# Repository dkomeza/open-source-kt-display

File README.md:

[![Contributors][contributors-shield]][contributors-url]
[![Forks][forks-shield]][forks-url]
[![Issues][issues-shield]][issues-url]
[![MIT License][license-shield]][license-url]

# Open-Source KT Display
Open source display firmware for E-Bike KT controllers. Made for Arduino with compatible SPI Display. 

**NOTE**: _This repository is no longer supported or updated by @dkomeza. It has been moved to [oskd](https://github.com/dkomeza/oskd) where it will be maintained from now on (21.01.2024). If you wish to continue to develop this code yourself, I recommend you fork it._</code>

<br>

## TL;DR
This is an open source display created for KT controllers. It uses ESP32 and a compatible SPI display. It is a work in progress and is not yet ready for production.

<br>

## Table of contents

- [Open-Source KT Display](#open-source-kt-display)
  - [TL;DR](#tldr)
  - [Table of contents](#table-of-contents)
  - [About the project](#about-the-project)
    - [Features](#features)
    - [Future of the project](#future-of-the-project)

<br><br>

## About the project

This project started as a way to use a torque sensor with the KT controllers. Later I decided to create a full featured display for the KT controllers. The goal is to create a display that is open source and can be used with any KT controller. It will also have a torque sensor input and a legal speed and power limiter. It is still a work in progress and is not yet ready for production. For more information about the project, please visit the [wiki](https://github.com/dkomeza/open-source-kt-display/wiki).

<br>

### Features
 - Open source
 - Cheap to build yourself
 - Has a torque sensor input
 - Has a legal speed and power limiter
<br>

### Future of the project

As for now, the project is still in development. I am working on the firmware and the hardware. The firmware is finally usable but still not final and the hardware is not yet ready for production. On the software side I am currently working on the settings menu and bug fixes, and on the hardware I am working on the PCB design and the case design. I will release the firmware and the hardware design files when they are ready. I will also release a tutorial on how to build the display yourself.

<!-- MARKDOWN LINKS & IMAGES -->
<!-- https://www.markdownguide.org/basic-syntax/#reference-style-links -->
[contributors-shield]: https://img.shields.io/github/contributors/dkomeza/open-source-kt-display.svg?style=for-the-badge
[contributors-url]: https://github.com/dkomeza/open-source-kt-display/graphs/contributors
[forks-shield]: https://img.shields.io/github/forks/dkomeza/open-source-kt-display.svg?style=for-the-badge
[forks-url]: https://github.com/dkomeza/open-source-kt-display/network/members
[stars-shield]: https://img.shields.io/github/stars/dkomeza/open-source-kt-display.svg?style=for-the-badge
[stars-url]: https://github.com/dkomeza/open-source-kt-display/stargazers
[issues-shield]: https://img.shields.io/github/issues/dkomeza/open-source-kt-display.svg?style=for-the-badge
[issues-url]: https://github.com/dkomeza/open-source-kt-display/issues
[license-shield]: https://img.shields.io/github/license/dkomeza/open-source-kt-display.svg?style=for-the-badge
[license-url]: https://github.com/dkomeza/open-source-kt-display/blob/master/LICENSE.txt

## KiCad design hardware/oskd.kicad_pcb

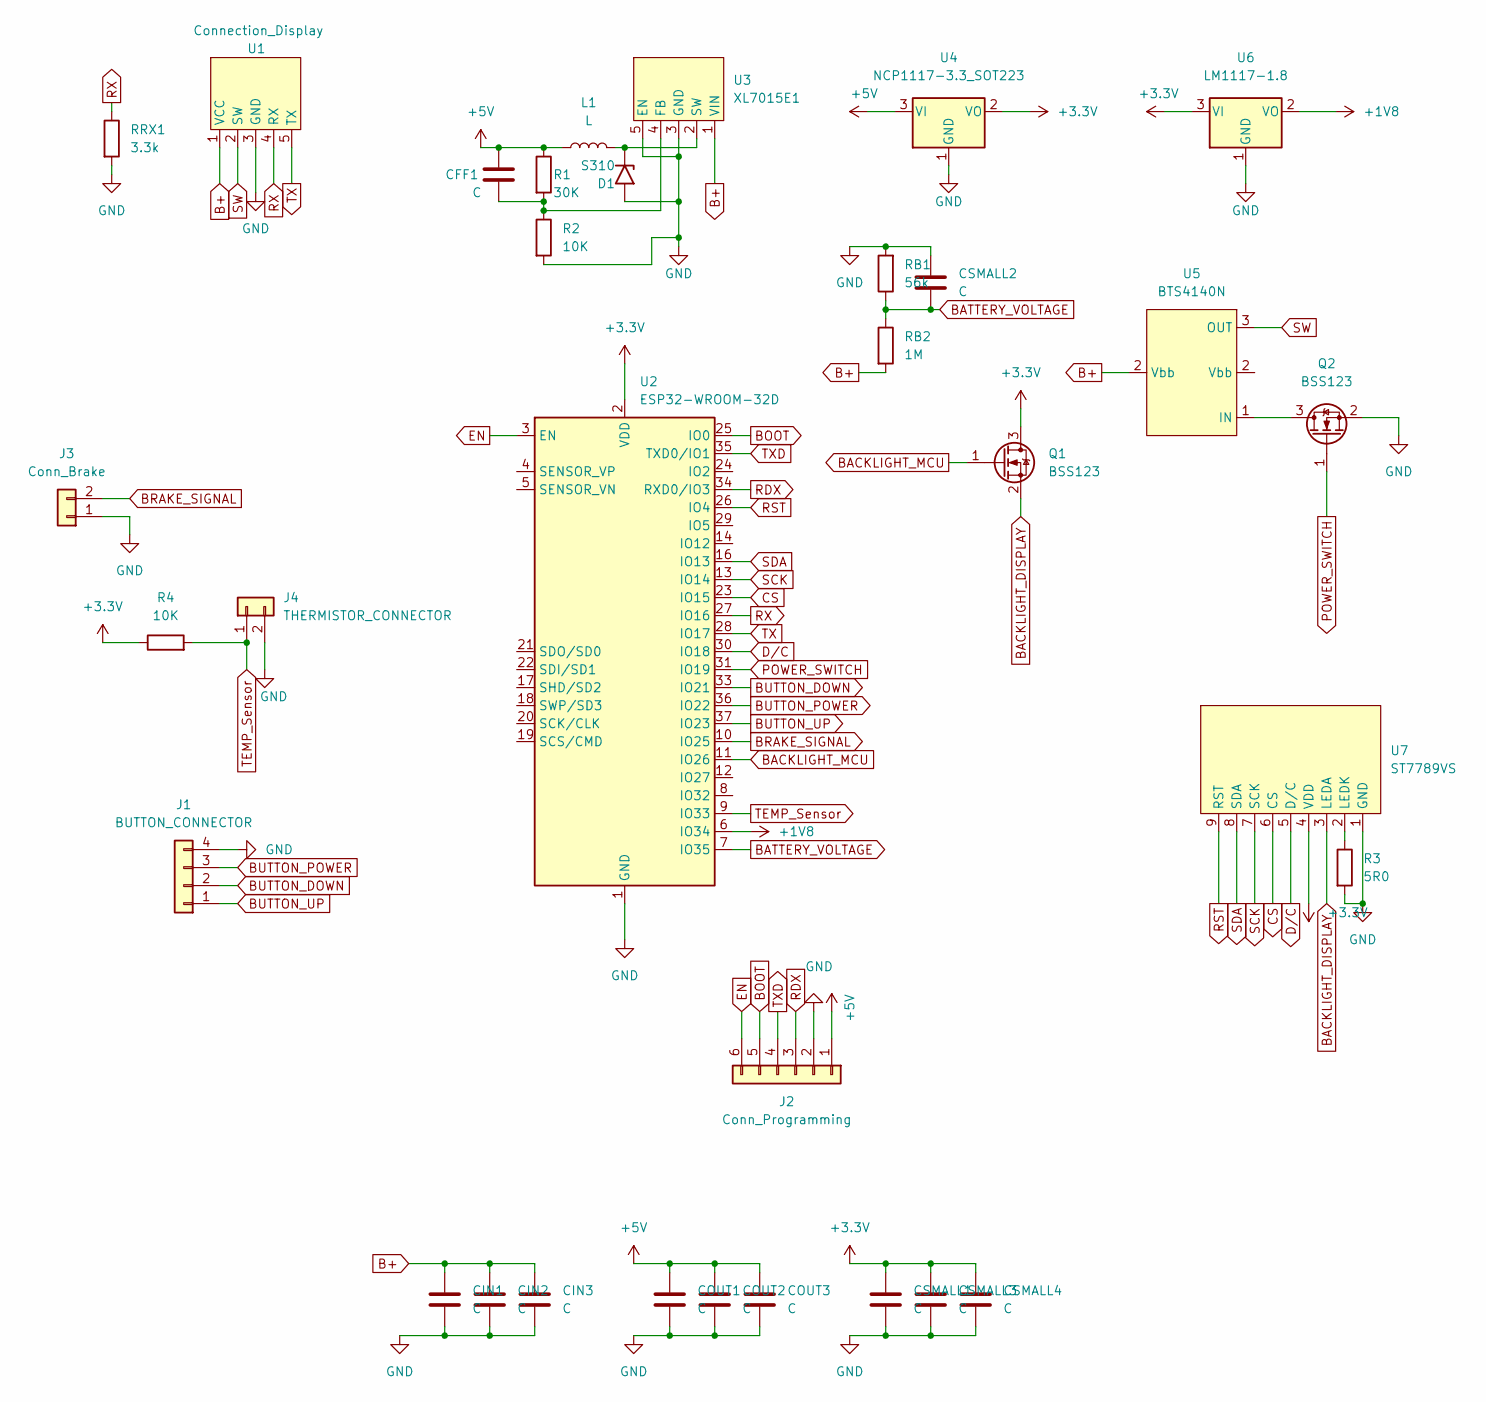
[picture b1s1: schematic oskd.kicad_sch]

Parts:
CFF1: C; C_1206_3216Metric_Pad1.33x1.80mm_HandSolder
CIN1, CIN2, CIN3: C; C_1210_3225Metric_Pad1.33x2.70mm_HandSolder
COUT1, COUT2, COUT3: C; C_1210_3225Metric_Pad1.33x2.70mm_HandSolder
CSMALL1, CSMALL2, CSMALL3, CSMALL4: C; C_1206_3216Metric
D1: S310; S2M
J1: BUTTON_CONNECTOR; SolderWire-1x4-buttons
J2: Conn_Programming; PinHeader_1x06_P2.54mm_Horizontal
J3: Conn_Brake; SolderWire-0.25sqmm_1x02_P4.5mm_D0.65mm_OD2mm
J4: THERMISTOR_CONNECTOR; SolderWire-0.25sqmm_1x02_P4.2mm_D0.65mm_OD1.7mm
L1: L; L_7.3x7.3_H3.5
Q1, Q2: BSS123; SOT-23
R1: 30K; R_1206_3216Metric_Pad1.30x1.75mm_HandSolder
R2, R4: 10K; R_1206_3216Metric_Pad1.30x1.75mm_HandSolder
R3: 5R0; R_1206_3216Metric_Pad1.30x1.75mm_HandSolder
RB1: 56k; R_1206_3216Metric_Pad1.30x1.75mm_HandSolder
RB2: 1M; R_1206_3216Metric_Pad1.30x1.75mm_HandSolder
RRX1: 3.3k; R_1206_3216Metric_Pad1.30x1.75mm_HandSolder
U1: Connection_Display; SolderWire-1x5-display
U2: ESP32-WROOM-32D; ESP32-WROOM-32
U3: XL7015E1; TO-252-5_TabPin3
U4: NCP1117-3.3_SOT223; SOT-223-3_TabPin2
U5: BTS4140N; SOT-223-3_TabPin2
U6: LM1117-1.8; SOT-223-3_TabPin2
U7: ST7789VS; ST7789V2

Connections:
+1V8: U2.6 (IO34), U6.2 (VO)
+3.3V: CSMALL1.1, CSMALL3.1, CSMALL4.1, Q1.3 (D), R4.1, U2.2 (VDD), U4.2 (VO), U6.3 (VI), U7.4 (VDD)
+5V: CFF1.2, COUT1.1, COUT2.1, COUT3.1, J2.1, L1.1, R1.1, U4.3 (VI)
B+: CIN1.1, CIN2.1, CIN3.1, RB2.2, U1.1 (VCC), U3.1 (VIN), U5.2 (Vbb)
BACKLIGHT_DISPLAY: Q1.2 (S), U7.3 (LEDA)
BACKLIGHT_MCU: Q1.1 (G), U2.11 (IO26)
BATTERY_VOLTAGE: CSMALL2.2, RB1.1, RB2.1, U2.7 (IO35)
BOOT: J2.5, U2.25 (IO0)
BRAKE_SIGNAL: J3.2, U2.10 (IO25)
BUTTON_DOWN: J1.2, U2.33 (IO21)
BUTTON_POWER: J1.3, U2.36 (IO22)
BUTTON_UP: J1.1, U2.37 (IO23)
CS: U2.23 (IO15), U7.6 (CS)
D/C: U2.30 (IO18), U7.5 (D/C)
EN: J2.6, U2.3 (EN)
GND: CIN1.2, CIN2.2, CIN3.2, COUT1.2, COUT2.2, COUT3.2, CSMALL1.2, CSMALL2.1, CSMALL3.2, CSMALL4.2, D1.2 (A2), J1.4, J2.2, J3.1, J4.2, Q2.2 (S), R2.2, R3.2, RB1.2, RRX1.2, U1.3 (GND), U2.1 (GND), U2.15 (GND), U2.38 (GND), U2.39 (GND), U3.3 (GND), U3.5 (EN), U4.1 (GND), U6.1 (GND), U7.1 (GND)
unnamed: CFF1.1, R1.2, R2.1, U3.4 (FB)
unnamed: D1.1 (A1), L1.2, U3.2 (SW)
unnamed: Q2.3 (D), U5.1 (IN)
unnamed: R3.1, U7.2 (LEDK)
POWER_SWITCH: Q2.1 (G), U2.31 (IO19)
RDX: J2.3, U2.34 (RXD0/IO3)
RST: U2.26 (IO4), U7.9 (RST)
RX: RRX1.1, U1.4 (RX), U2.27 (IO16)
SCK: U2.13 (IO14), U7.7 (SCK)
SDA: U2.16 (IO13), U7.8 (SDA)
SW: U1.2 (SW), U5.3 (OUT)
TEMP_Sensor: J4.1, R4.2, U2.9 (IO33)
TX: U1.5 (TX), U2.28 (IO17)
TXD: J2.4, U2.35 (TXD0/IO1)

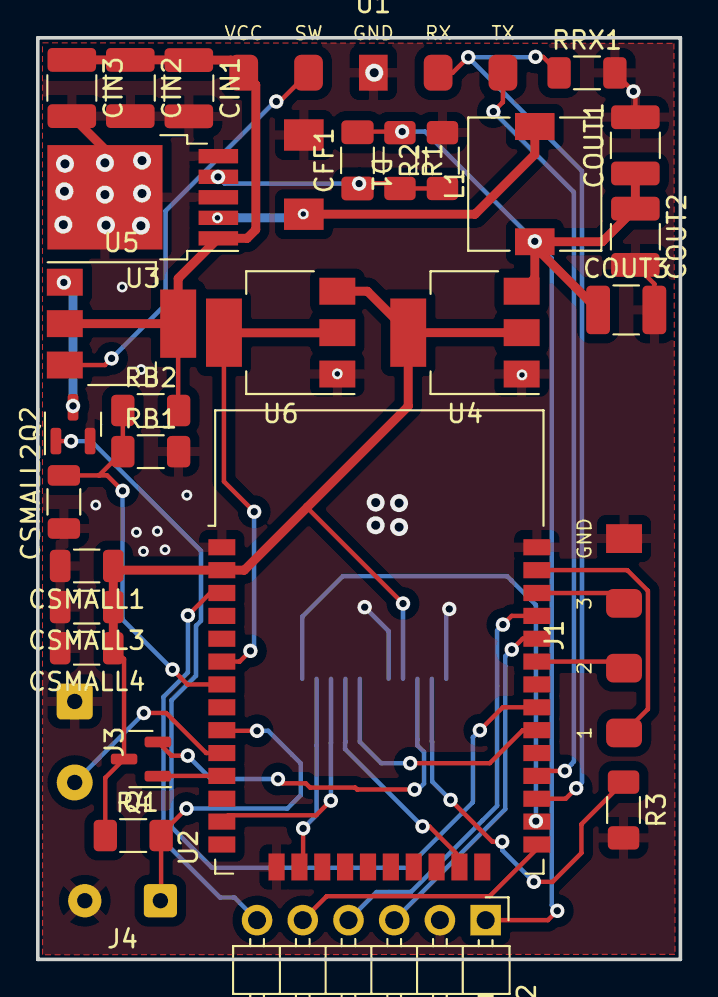
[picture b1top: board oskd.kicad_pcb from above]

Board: 2 copper layers, 35.7 x 51.2 mm, 33 parts (1 on the bottom side), 30 nets.

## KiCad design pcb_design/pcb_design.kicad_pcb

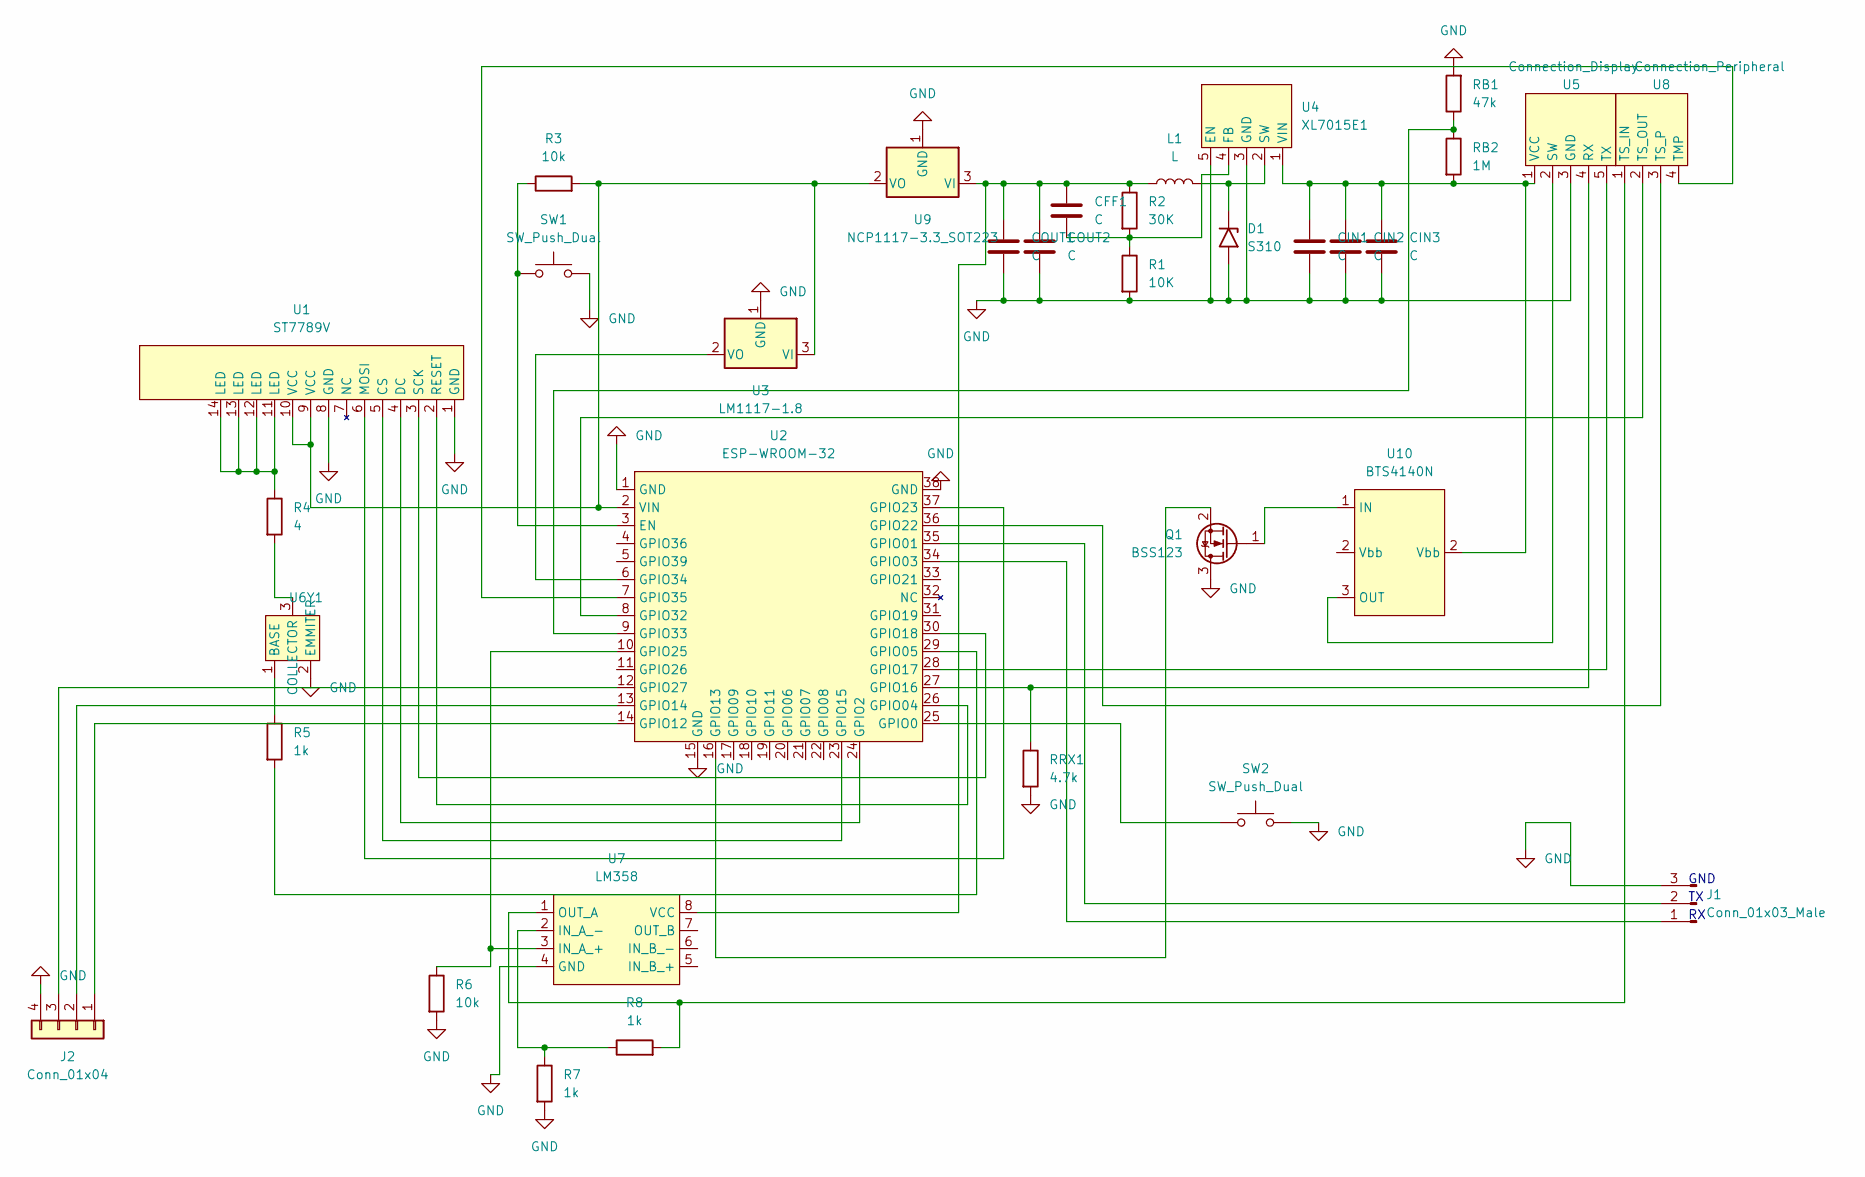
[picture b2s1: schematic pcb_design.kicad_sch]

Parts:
CFF1: C; C_1206_3216Metric_Pad1.33x1.80mm_HandSolder
CIN1, CIN2, CIN3: C; C_1210_3225Metric_Pad1.33x2.70mm_HandSolder
COUT1, COUT2: C; C_1210_3225Metric_Pad1.33x2.70mm_HandSolder
D1: S310; S2M
J1: Conn_01x03_Male; PinHeader_1x03_P1.00mm_Vertical
J2: Conn_01x04; SolderWire-1x4-buttons
L1: L; L_7.3x7.3_H3.5
Q1: BSS123; SOT-23
R1: 10K; R_1206_3216Metric_Pad1.30x1.75mm_HandSolder
R2: 30K; R_1206_3216Metric_Pad1.30x1.75mm_HandSolder
R3, R6: 10k; R_1206_3216Metric_Pad1.30x1.75mm_HandSolder
R4: 4; R_1206_3216Metric_Pad1.30x1.75mm_HandSolder
R5, R7, R8: 1k; R_1206_3216Metric_Pad1.30x1.75mm_HandSolder
RB1: 47k; R_1206_3216Metric_Pad1.30x1.75mm_HandSolder
RB2: 1M; R_1206_3216Metric_Pad1.30x1.75mm_HandSolder
RRX1: 4.7k; R_1206_3216Metric_Pad1.30x1.75mm_HandSolder
SW1, SW2: SW_Push_Dual; SW1
U1: ST7789V
U2: ESP-WROOM-32; ESP32-WROOM-32
U3: LM1117-1.8; SOT-223-3_TabPin2
U4: XL7015E1; TO-252-5_TabPin3
U5: Connection_Display; SolderWire-1x5-display
U6: Y1; SOT-23
U7: LM358; SO-8_5.3x6.2mm_P1.27mm
U8: Connection_Peripheral; SolderWire-1x4-ts
U9: NCP1117-3.3_SOT223; SOT-223-3_TabPin2
U10: BTS4140N; SOT-223-3_TabPin2

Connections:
unnamed: CFF1.1, R1.1, R2.2, U4.4 (FB)
unnamed: CFF1.2, COUT1.1, COUT2.1, L1.1, R2.1, U7.8 (VCC), U9.3 (VI)
unnamed: CIN1.1, CIN2.1, CIN3.1, RB2.2, U4.1 (VIN), U5.1 (VCC), U10.2 (Vbb)
unnamed: D1.1 (A1), L1.2, U4.2 (SW)
unnamed: J1.1, U2.34 (GPIO03)
unnamed: J1.2, U2.35 (GPIO01)
unnamed: J2.1, U2.14 (GPIO12)
unnamed: J2.2, U2.13 (GPIO14)
unnamed: J2.3, U2.12 (GPIO27)
unnamed: Q1.1 (G), U10.1 (IN)
unnamed: Q1.2 (S), U2.16 (GPIO13)
unnamed: R3.1, SW1.1, U2.3 (EN)
unnamed: R3.2, U1.9 (VCC), U1.10 (VCC), U2.2 (VIN), U3.3 (VI), U9.2 (VO)
unnamed: R4.1, U1.11 (LED), U1.12 (LED), U1.13 (LED), U1.14 (LED)
unnamed: R4.2, U6.3 (COLLECTOR)
unnamed: R5.1, U6.1 (BASE)
unnamed: R5.2, U2.29 (GPIO05)
unnamed: R6.1, U2.10 (GPIO25), U7.3 (IN_A_+)
unnamed: R7.1, R8.1, U7.2 (IN_A_-)
unnamed: R8.2, U7.1 (OUT_A), U8.1 (TS_IN)
unnamed: RB1.1, RB2.1, U2.9 (GPIO33)
unnamed: RRX1.1, U2.27 (GPIO16), U5.4 (RX)
unnamed: SW2.1, U2.25 (GPIO0)
unnamed: U1.2 (RESET), U2.26 (GPIO04)
unnamed: U1.3 (SCK), U2.30 (GPIO18)
unnamed: U1.4 (DC), U2.24 (GPIO2)
unnamed: U1.5 (CS), U2.23 (GPIO15)
unnamed: U1.6 (MOSI), U2.37 (GPIO23)
unnamed: U2.6 (GPIO34), U3.2 (VO)
unnamed: U2.8 (GPIO32), U8.2 (TS_OUT)
unnamed: U2.28 (GPIO17), U5.5 (TX)
unnamed: U2.36 (GPIO22), U8.3 (TS_P)
unnamed: U5.2 (SW), U10.3 (OUT)

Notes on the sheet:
GND

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
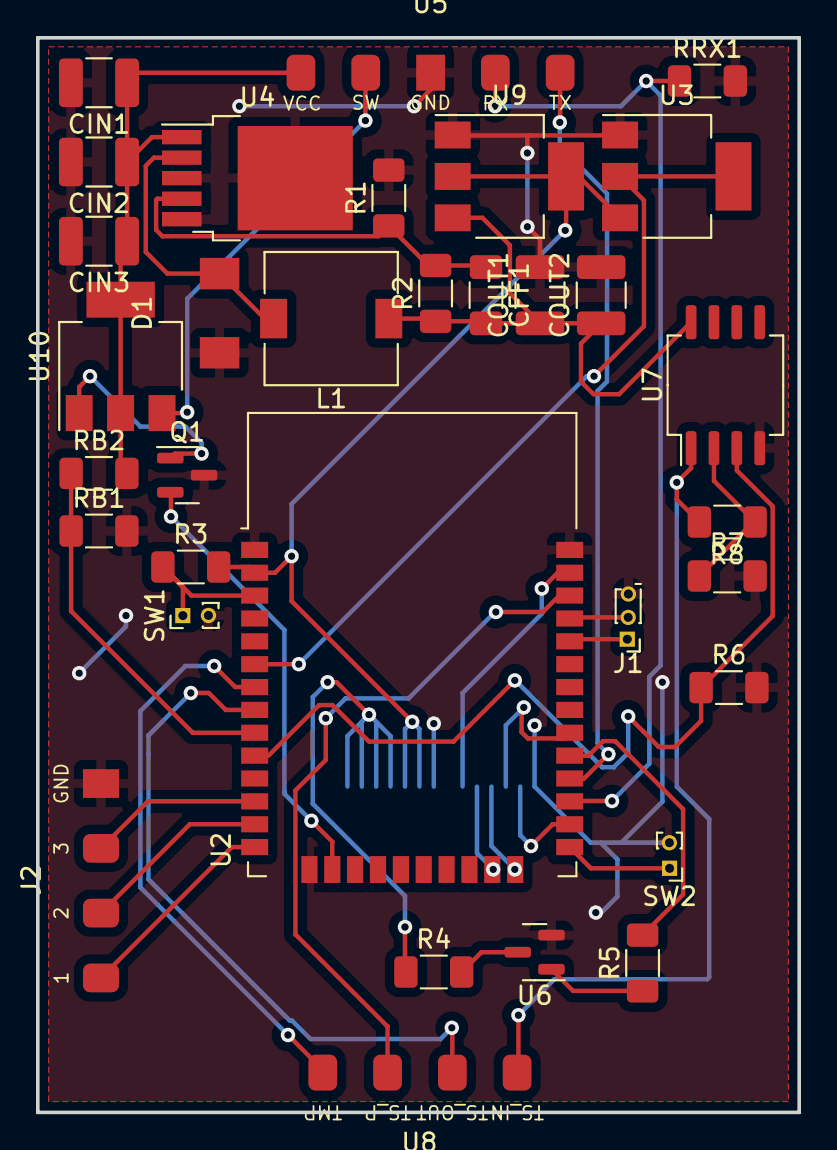
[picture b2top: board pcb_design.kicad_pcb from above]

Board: 2 copper layers, 42.3 x 59.7 mm, 34 parts (1 on the bottom side), 35 nets.

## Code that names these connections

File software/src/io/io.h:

#ifndef OSKD_IO_H
#define OSKD_IO_H

#include <Arduino.h>
#include <button.h>

#include "../data/data.h"
#include "../settings/settings.h"

class IO
{
public:
    void setup();
    void update();

private:
    const int BATTERY_VOLTAGE_PIN = 35;
    const int BATTERY_VOLTAGE_OFFSET_PIN = 34;
    const int BUTTON_DOWN_PIN = 14;
    const int BUTTON_POWER_PIN = 27;
    const int BUTTON_UP_PIN = 12;

    Button buttonDown = Button(this->BUTTON_DOWN_PIN);
    Button buttonPower = Button(this->BUTTON_POWER_PIN);
    Button buttonUp = Button(this->BUTTON_UP_PIN);

    int voltageOffset = 0;
    int getVoltageOffset();
    double getBatteryVoltage();
};

extern IO io;

#endif // OSKD_IO_H

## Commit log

2022-09-12 README updates
2022-09-12 Understanding Communication protocol
2022-09-13 Arduino button prototype
2022-09-13 Initial thermistor code
2022-09-13 Upload thermistor circuit
2022-09-13 Button circuit diagram upload
2022-09-13 Added README to Arduino tests
2022-09-13 [ImgBot] Optimize images
    *Total -- 21.88kb -> 8.84kb (59.63%)
    /testing/Arduino/button/button_circuit.png -- 9.76kb -> 3.85kb (60.53%)
    /testing/Arduino/thermistor/thermistor_circuit.png -- 12.13kb -> 4.99kb (58.9%)
2022-09-14 Created React website using create-react-app
2022-09-15 Installed sass package
2022-09-15 Added basic sass files
2022-09-15 Form testing
2022-09-15 Initial website design
2022-09-18 Documentation update
2022-10-01 Protocol update
2022-10-02 Protocol wheel size testing
2022-10-04 Web calculator updates
2022-10-04 Read serial communication
2022-10-05 Serial read documentation update
2022-10-05 Finished web calculator
2022-10-05 Wheel size option update
2022-10-05 Select readability improvement
2022-10-05 Added copy functionality
2022-10-05 First beta. (only one way communication)
2022-10-05 Small web calculator updates
2022-10-06 Beta v0.2 - Both way communication
2022-10-07 First beta release
2022-10-11 Adapted code to use ESP32 instead of Arduino Nano
2022-10-17 Added libraries to release folder && small updates
2022-10-17 [ImgBot] Optimize images
    *Total -- 1,143.09kb -> 876.52kb (23.32%)
    /testing/Arduino/serial_read_v1.0/serial_circuit.png -- 22.34kb -> 6.39kb (71.39%)
    /release/libraries/TFT_eSPI/examples/PNG Images/LittleFS_PNG/data/panda.png -- 178.47kb -> 108.92kb (38.97%)
    /release/libraries/TFT_eSPI/examples/PNG Images/LittleFS_PNG_DMA/data/panda.png -- 178.47kb -> 108.92kb (38.97%)
    /release/libraries/TFT_eSPI/docs/RPi_TFT_connections/RPi_TFT_Connections.png -- 381.43kb -> 297.83kb (21.92%)
    /release/libraries/TFT_eSPI/examples/Sprite/Animated_dial/data/dial.jpg -- 17.67kb -> 15.59kb (11.77%)
2022-10-17 TFT_ESPI library cleanup
2022-10-17 OneButton library cleanup
2022-10-17 Protocol updates
2022-10-18 [ImgBot] Optimize images
    /testing/Arduino/serial_read_v1.0/serial_circuit.png -- 22.34kb -> 6.39kb (71.39%)
2022-10-18 Code cleanup && added comments
2022-10-18 Added EEPROM functionality
2022-10-19 Small bug fixes
2022-10-19 Major bug fixes
2022-10-19 File structure update
2022-10-20 Speed diplay bug fix
2022-10-29 Bug fixes & test mode improvement
2022-10-30 Engine temperature display fix
2022-11-01 Bug fixes
2022-11-01 Engine temp display fix
2022-11-01 Added braking mode indicator
2022-11-01 Braking indicator bug fixes
2022-11-02 Braking mode bug fix
2022-11-09 Bump loader-utils in /prototype/web-parameters-calculator
    Bumps [loader-utils](https://github.com/webpack/loader-utils) from 2.0.2 to 2.0.3.
    - [Release notes](https://github.com/webpack/loader-utils/releases)
    - [Changelog](https://github.com/webpack/loader-utils/blob/v2.0.3/CHANGELOG.md)
    - [Commits](https://github.com/webpack/loader-utils/compare/v2.0.2...v2.0.3)
    ---
    updated-dependencies:
2022-11-16 Bump loader-utils in /prototype/web-parameters-calculator
    Bumps [loader-utils](https://github.com/webpack/loader-utils) from 2.0.3 to 2.0.4.
    - [Release notes](https://github.com/webpack/loader-utils/releases)
    - [Changelog](https://github.com/webpack/loader-utils/blob/v2.0.4/CHANGELOG.md)
    - [Commits](https://github.com/webpack/loader-utils/compare/v2.0.3...v2.0.4)
    ---
    updated-dependencies:
2022-11-26 Initial menu idea
2022-11-26 Documentation updates
2022-11-27 Change indentation width
2022-11-27 Reset cursor position after exiting menu
2022-11-27 Final menu look and logic
2022-11-27 Added packet calculation
2022-11-27 Final settings menu changes
2022-11-27 Moved array size from const int to define
2022-11-27 Merged settings menu into the release
2022-11-27 File cleanup
2022-12-07 style deleted unused comment
2022-12-07 style deleted unused variables
2022-12-07 style rename variable names
2022-12-07 style comments cleanup
2022-12-07 Fixed settings when powering on the first time
2022-12-07 Variable names fix
2022-12-08 Read, calculate and output torque
2022-12-10 Torque sensor basic implementation
2022-12-10 Added menu option for setting torque sensor delay (T1)
2022-12-10 Fixed torque sensor output
2022-12-13 CodeQL improvements
2022-12-13 Added comments
2022-12-14 Initial torque sensor gear support
2022-12-15 Function name change
2022-12-15 Added battery voltage reading
2022-12-15 Battery offset fix
2022-12-15 Changed battery voltage display location
2022-12-16 Battery voltage fix
2023-01-09 Bump json5 from 1.0.1 to 1.0.2 in /prototype/web-parameters-calculator
    Bumps [json5](https://github.com/json5/json5) from 1.0.1 to 1.0.2.
    - [Release notes](https://github.com/json5/json5/releases)
    - [Changelog](https://github.com/json5/json5/blob/main/CHANGELOG.md)
    - [Commits](https://github.com/json5/json5/compare/v1.0.1...v1.0.2)
    ---
    updated-dependencies:
2023-01-24 Major changes:
    - Added OTA support
    - Split code into multiple files
    - Added settings file
    - Added display file
2023-01-25 Project structure change.
    - Deleted the web calculator (the display has one built in)
    - Deleted testing directory
    - Moved the source files to the main directory
2023-01-25 Torque sensor file bug fixes
2023-01-25 Initial file structure
2023-01-25 Moved functions to the logic file.
2023-01-25 Moved functions to logic file.
2023-01-25 Moved logic to logic file.
2023-01-25 Compilation bug fixes.
2023-01-25 Moved handleLimit function to settings file.
2023-01-25 Bug fixes.
2023-01-25 T1 parameter fix.
2023-01-26 Added JSdoc to the logic file.
2023-01-26 Added JSdoc to the settings file.
2023-01-26 Added JSdoc to the torqueSensor file.
2023-01-26 Added pcb design
2023-02-03 Battery level display fix
2023-02-03 Changed P4 and C4 settings for the torque sensor
2023-02-03 Added embold config file
2023-02-03 Braking icon fix
2023-02-10 Created custom button implementation
2023-03-21 Major updates
2023-04-06 Switch to PlatformIO
2023-04-06 Move .git directory
2023-04-06 Initial sleep implementation
2023-04-06 Boot after holding the power button for one second
2023-04-07 Move the display init to prevent flash of white on restart
2023-04-07 Added shutdown timeout setting
2023-04-07 Shutdown after inactivity
2023-06-09 :art: Change file structure
2023-06-09 :zap: Switch from .h files to .hpp
2023-07-08 :bug: Fix display not initializing
2023-07-08 :fire: Remove old code
2023-07-08 :sparkles: Add `controller` and `OTA` files
2023-07-08 :sparkles: Add screen class
2023-07-08 :bulb: Document `credentials.h` file
2023-07-08 :sparkles: Add `data` class
2023-07-08 :sparkles: Add `settings` class
2023-07-08 :sparkles: Add `io` class
2023-07-08 :heavy_plus_sign: Add includes in main file
2023-07-08 :sparkles: Add `setupOTA` function
2023-07-08 :hammer: Refactor `settings` class
    Not complete - missing settings menu
2023-07-08 :hammer: Refactor settings and screen
2023-07-08 :construction: Wait for testing
    Initial refactor done, waiting for testing
2023-07-08 :zap: General update
2023-07-09 :construction: Add screen fonts
2023-07-10 :construction: Work on settings menu
2023-07-10 :construction: Update settings menu
2023-07-10 :sparkles: Finish refactor.
2023-07-11 :sparkles: Power switch & bug fixes
2023-07-11 :bulb: Add `credentials.h` template
2023-09-12 :zap: Major updates
2023-11-14 :truck: Restart the project development
2023-11-14 :sparkles: Move button library
2023-11-16 :books: Add TFT setup
2023-11-16 :sparkles: Add basic main loop
2023-11-16 :sparkles: Add OTA support
2023-11-16 :sparkles: Add file for managing buttons
2023-11-16 :sparkles: Setup buttons
2023-11-17 :hammer: Move constants to the .cpp file
2023-11-17 :sparkles: Add buttons to the main loop
2023-11-17 :sparkles: Create Data file
    Data file used for sharing data across modules
2023-11-17 :sparkles: Add screen fonts
2023-11-18 :sparkles: Create TFT class
